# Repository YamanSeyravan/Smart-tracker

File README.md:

# Smart-tracker
A tracker in a smartwatch design equipped with STM32 and GPS+GSM system and motion sensors for enhanced tracking.
This project is not fully ready yet for Sch, Gerber and assembly files or any info contact me.

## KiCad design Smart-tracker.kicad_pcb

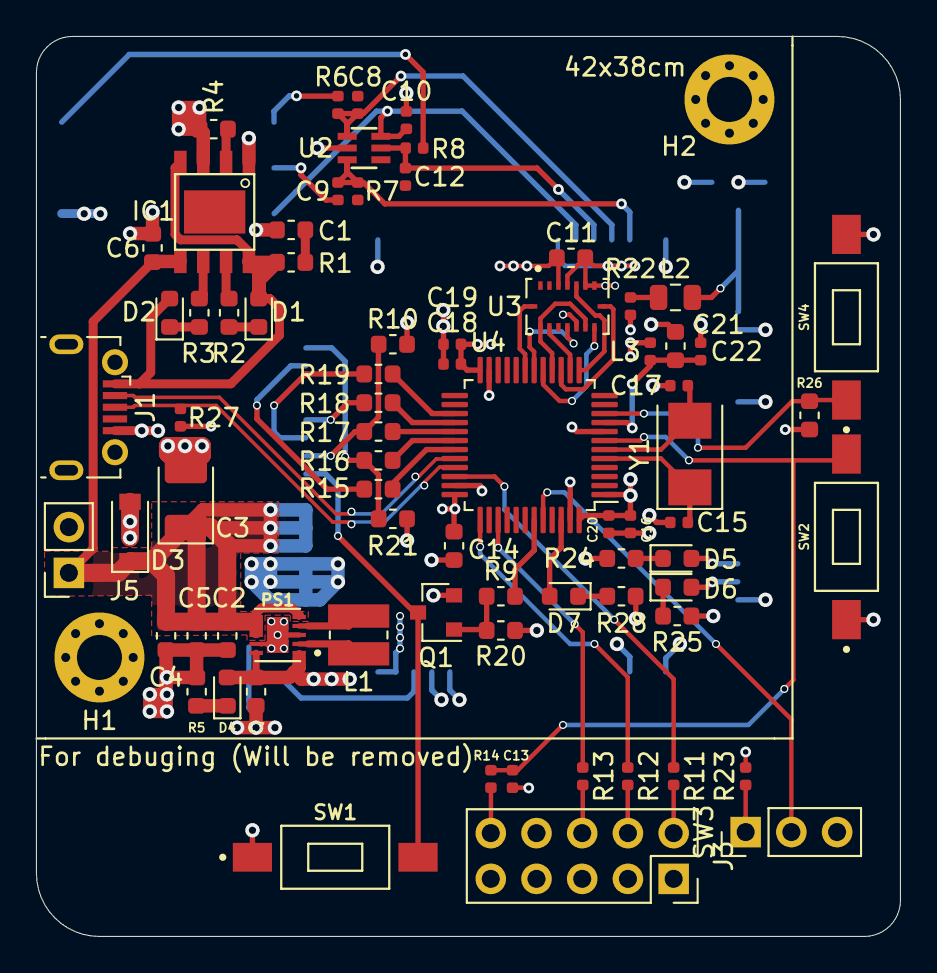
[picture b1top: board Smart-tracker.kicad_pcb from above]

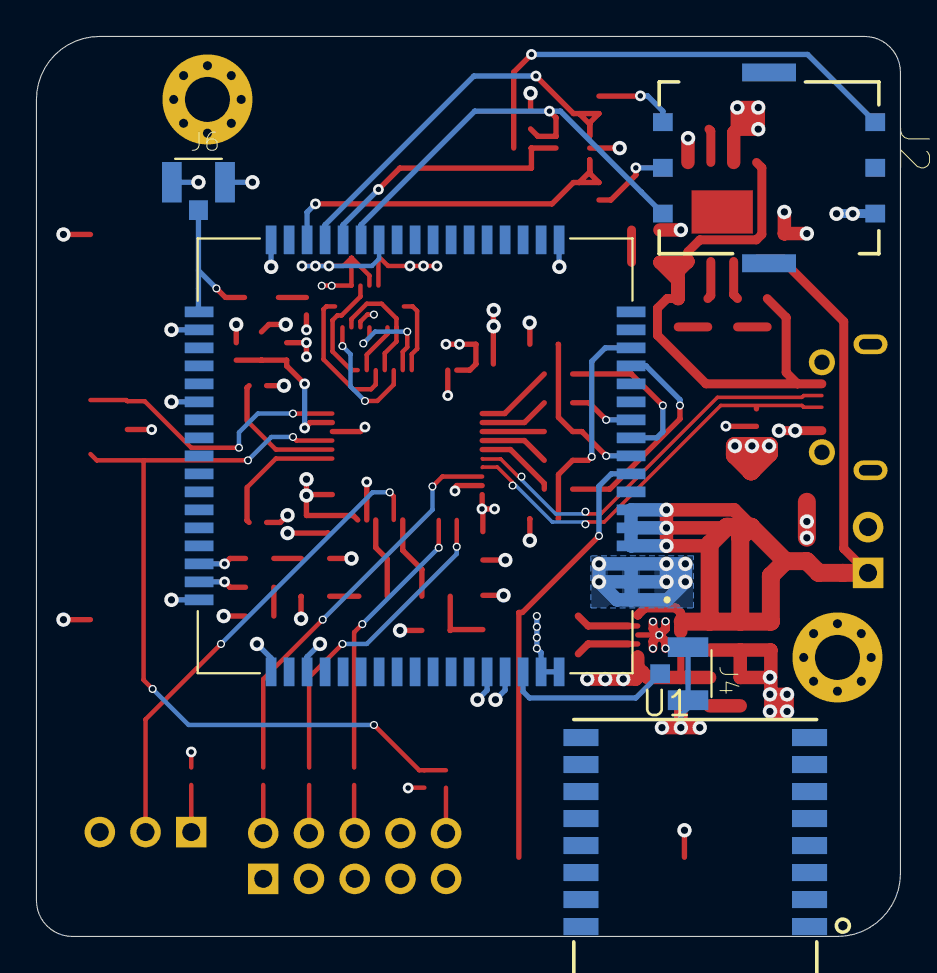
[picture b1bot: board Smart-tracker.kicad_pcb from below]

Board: 4 copper layers, 48.0 x 50.0 mm, 81 parts (5 on the bottom side), 65 nets.

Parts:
C1, C6, C7: 10u; C_0603_1608Metric
C2: 4.7u; C_0603_1608Metric
C3: 100u; CP_EIA-3528-21_Kemet-B
C4: 33p; C_0603_1608Metric
C5: 10p; C_0603_1608Metric
C8, C9, C12: 33p; C_0402_1005Metric
C10, C13, C16, C18, C19, C20, C22: 100n; C_0402_1005Metric
C11, C21: 1u; C_0603_1608Metric
C14: 4u7; C_0603_1608Metric
C15, C17: 30p; C_0402_1005Metric
D1: Red; LED_0603_1608Metric
D2, D5: Green; LED_0603_1608Metric
D3: MMSZ5231BT1G; D_SOD-123
D4: GREEN; LED_0603_1608Metric
D6: Blue; LED_0603_1608Metric
D7: BLUE; LED_0603_1608Metric
H1, H2: MountingHole_Pad; MountingHole_2.5mm_Pad_Via
IC1: TP4056; SOP-8
J1: USB_B_Micro; USB_Micro_JLCPCB
J2: SIM8050-6-0-14-01-X_REVF; GCT_SIM8050-6-0-14-01-X_REVF
J3: SWD; PinSocket_2x05_P2.54mm_Vertical
J4, J6: U.FL-R-SMT(01); HRS_U.FL-R-SMT(01)
J5: Power; PinSocket_1x02_P2.54mm_Vertical
L1: 1.5u; L_Wuerth_MAPI-3015
L2: 68uh; L_0805_2012Metric
L3: 27n; L_0402_1005Metric
PS1: TPS63031DSKR; SON50P250X250X80-11N
Q1: MMBT3904; SOT-23
R1: 1; R_0603_1608Metric
R2, R3, R5, R15, R16, R17, R18, R19, R24, R25, R28: 1k; R_0603_1608Metric
R4: 2k; R_0603_1608Metric
R6, R7, R8, R11, R12, R13, R14, R22: 22; R_0402_1005Metric
R9, R20: 47k; R_0603_1608Metric
R10, R21: 5.6k; R_0603_1608Metric
R23: 10k; R_0402_1005Metric
R26: 10k; R_0603_1608Metric
R27: 1k5; R_0402_1005Metric
SW1, SW2, SW4: SW_Push; SW_1437566-4
SW3: SW_SPDT; PinHeader_1x03_P2.54mm_Vertical
U1: SIM808; XCVR_SIM808
U2: SMF05CT1G; SOT65P210X110-6N
U3: BMI088; PQFN50P450X300X100-16N
U4: STM32F103C8T6; LQFP-48_7x7mm_P0.5mm
U5: 317030001; XCVR_317030001
Y1: 8MHz; Crystal_SMD_5032-2Pin_5.0x3.2mm

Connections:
+3.3VA: C21.1, C22.1, L3.2, U4.9
+3V3: C7.1, C11.1, C14.1, C16.1, C18.1, C19.1, C20.1, D4.2, J3.1, L3.1, PS1.1, PS1.10, R22.2, R26.1, R27.1, SW3.3, U3.3, U3.11, U4.1, U4.24, U4.36, U4.48
+5V: D1.2, D2.2, IC1.4, IC1.8, J1.1, R1.1
/BOOT0: SW3.2, U4.44
/HSE_IN: C17.1, U4.6, Y1.2
/HSE_OUT: C15.1, U4.5, Y1.1
DATA: J2.C7, R8.2
DCD: R18.1, U4.28
DTR: R17.1, U4.29
GND: C1.2, C2.2, C3.2, C4.2, C5.2, C6.2, C7.2, C10.1, C11.2, C13.2, C14.2, C15.2, C16.2, C17.2, C18.2, C19.2, C20.2, C21.2, C22.2, D3.2, H1.1, H2.1, IC1.1, IC1.3, J1.5, J1.6, J2.C5, J3.3, J3.5, J3.9, J4.1, J4.2, J5.2, J6.1, J6.2, PS1.3, PS1.9, PS1.11, Q1.2, R4.2, R5.2, R10.1, R20.1, R21.1, R23.2, R24.2, R25.2, R28.2, SW1.1, SW2.1, SW4.2, U1.1, U1.2, U1.3, U1.18, U1.28, U1.34, U1.36, U1.40, U1.51, U1.52, U1.54, U1.64, U1.65, U1.67, U1.68, U2.2, U3.4, U3.6, U3.7, U4.8, U4.23, U4.35, U4.47
GPS: J6.3, L2.2, U1.35
GSM: J4.3, U1.66
INT_ACC: U3.16, U4.19
INT_GYR: U3.12, U4.18
MISO: U3.10, U3.15, U4.16
MOSI: U3.9, U4.17
NRST: C13.1, R14.1, SW2.2, U4.7
NSS1: U3.14, U4.14
NSS2: U3.5, U4.13
Net: D6.2, U1.50
unnamed: C1.1, R1.2
unnamed: D1.1, R2.2
unnamed: D2.1, R3.2
unnamed: D4.1, R5.1
unnamed: D5.1, R24.1
unnamed: D6.1, R25.1
unnamed: D7.1, R28.1
unnamed: IC1.2, R4.1
unnamed: IC1.6, R3.1
unnamed: IC1.7, R2.1
unnamed: J2.C2, R7.1
unnamed: J2.C3, R6.1
unnamed: J3.2, R11.2
unnamed: J3.4, R12.2
unnamed: J3.6, R13.2
unnamed: J3.10, R14.2
unnamed: L1.1, PS1.2
unnamed: L1.2, PS1.4
unnamed: L2.1, R22.1
unnamed: Q1.1, R9.1, R20.2
unnamed: R23.1, SW3.1
PA0: R26.2, SW4.1, U4.10
PA5: U3.8, U4.15
PA9: R16.1, U4.30
PA10: R15.1, U4.31
PB7: R9.2, U4.43
PB9: D7.2, U4.46
PB14: R19.1, U4.27
PWRKEY: Q1.3, SW1.2, U1.8
SIM_CLK: C8.2, R6.2, U1.31, U2.1
SIM_DATA: C12.2, R8.1, U1.30, U2.5
SIM_DCD: R18.2, U1.11
SIM_DTR: R10.2, R17.2, U1.9
SIM_RING: R19.2, U1.10
SIM_RST: C9.2, R7.2, U1.32, U2.3
SIM_RXD: R16.2, R21.2, U1.15
SIM_TXD: R15.2, U1.14
SIM_VDD: C10.2, J2.C1, U1.29, U2.6
STA: D5.2, U1.49
SWCLK: R12.1, U4.37
SWDIO: R11.1, U4.34
SWO: R13.1, U4.39
USB_D+: J1.3, R27.2, U4.33
USB_D-: J1.2, U4.32
VBAT+: C2.1, C3.1, C4.1, C5.1, C6.1, D3.1, IC1.5, J5.1, PS1.5, PS1.6, PS1.7, PS1.8, U1.4, U1.5, U1.6

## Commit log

2021-02-18 Kicad PCB file and 3D module image added.
    For Sch and more info contact me.
2021-02-18 Readme update
    info added
